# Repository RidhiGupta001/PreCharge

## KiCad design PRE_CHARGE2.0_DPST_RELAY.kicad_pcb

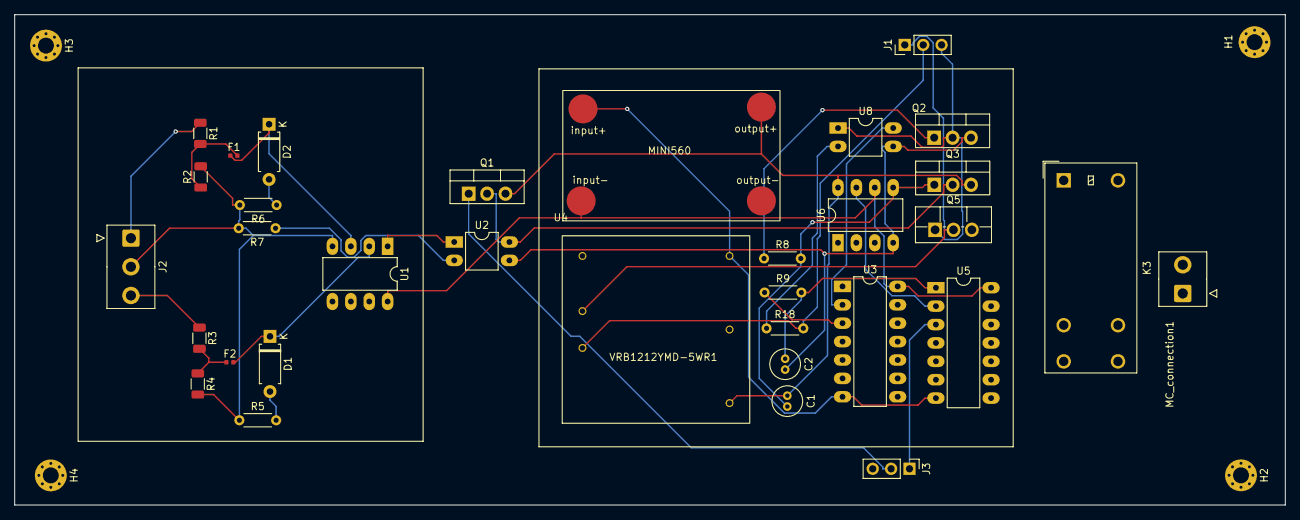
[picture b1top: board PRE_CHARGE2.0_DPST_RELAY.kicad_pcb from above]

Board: 2 copper layers, 175.5 x 67.7 mm, 37 parts (0 on the bottom side), 29 nets.

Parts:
C1: 10u; C_Radial_D4.0mm_H7.0mm_P1.50mm
C2: 47u; C_Radial_D4.0mm_H7.0mm_P1.50mm
D1, D2: PTVS12VZ1USK; D_A-405_P7.62mm_Horizontal
F1, F2: Fuse; Fuse_0402_1005Metric
H1, H2, H3, H4: MountingHole; MountingHole_2.2mm_M2_Pad_Via
J1: LV_INPUT_CONNECTIONS; PinHeader_1x03_P2.54mm_Vertical
J2: HV_INPUT_CONNECTIONS; TE_826576-3_1x03_P3.96mm_Vertical
J3: OUTPUTS; PinHeader_1x03_P2.54mm_Vertical
K3: G7L-2A-X DC24; Relay_DPST_Omron_G2RL-2A
MC_connection1: Conn_01x02; TE_826576-2_1x02_P3.96mm_Vertical
Q1, Q3: PMOS; TO-220-3_Vertical
Q2: NMOS; TO-220-3_Vertical
Q5: IRLIZ44N; TO-220F-3_Vertical
R1: 36M; R_1206_3216Metric
R2: 200k; R_1206_3216Metric
R3: 39M; R_1206_3216Metric
R4: 220k; R_1206_3216Metric
R5, R6: R_US; R_Axial_DIN0204_L3.6mm_D1.6mm_P5.08mm_Horizontal
R7, R18: 330; R_Axial_DIN0204_L3.6mm_D1.6mm_P5.08mm_Horizontal
R8: 560K; R_Axial_DIN0204_L3.6mm_D1.6mm_P5.08mm_Horizontal
R9: 18k; R_Axial_DIN0204_L3.6mm_D1.6mm_P5.08mm_Horizontal
U1, U6: LM358; DIP-8_W7.62mm_LongPads
U2, U8: NSL-32; DIP-4_W7.62mm_LongPads
U3: 4077; DIP-14_W7.62mm_LongPads
U4: AMS1117-5.0; mini560
U5: 74LS08; DIP-14_W7.62mm_LongPads
VRB1212YMD-5WR1: VRB1212YMD-5WR3

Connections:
5V: U1.8 (V+), U3.14 (VDD), U4.2 (VO), U5.14 (VCC), U6.6 (-)
12V: C1.1, Q1.3 (S), Q3.3 (S), U4.3 (VI), U6.8 (V+), VRB1212YMD-5WR1.3 (+Vo)
12V_GLV: J1.1, Q5.2 (D), VRB1212YMD-5WR1.1 (-Vin)
AIR+: J3.2, Q1.1 (D)
AIR/5s: Q1.2 (G), Q3.2 (G), U2.4 (R)
Earth: C2.2, Q2.3 (S), U2.3 (R), U6.4 (V-), U8.3 (R)
GNDREF: U3.7 (VSS), U4.1 (GND), U5.7 (GND), VRB1212YMD-5WR1.5 (GND)
LV_GND2: J1.2, R18.2, VRB1212YMD-5WR1.2 (+Vin)
MC+: J2.3, R3.1
unnamed: C2.1, R9.2, U5.1
unnamed: D1.2 (A), R5.2
unnamed: D1.1 (K), F2.2, U1.2 (-)
unnamed: D2.2 (A), R6.1
unnamed: D2.1 (K), F1.1, U1.3 (+)
unnamed: F1.2, R1.2, R2.1
unnamed: F2.1, R3.2, R4.1
unnamed: Q2.1 (D), R8.1
unnamed: C1.2, Q3.1 (D), R8.2, U6.5 (+)
unnamed: R9.1, U3.3
unnamed: U1.1, U2.1 (A)
unnamed: R7.1, U2.2 (K)
unnamed: U5.2, U6.7
unnamed: R18.1, U8.2 (K)
PR(TSMS): J1.3, Q2.2 (G), Q5.1 (G), U8.1 (A)
PR(TSMS)_ISOLATED: U3.2, U8.4 (R)
PreCharge_AUX: J3.3, U3.1
SafeState: J3.1, U5.3
TS+: J2.1, R1.1
TS-: J2.2, R2.2, R4.2, R5.1, R6.2, R7.2, U1.4 (V-)
